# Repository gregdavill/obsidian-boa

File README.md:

# Obsidian Boa #

     ~ Current Status: Prototype boards ordered from OSHPark ~
     
     Note: This design was performed in KiCad nightly , you will need a Nightly build to open and edit these source files.

## Bare PCBs:
Order some PCBs
     [OSHPark](https://oshpark.com/shared_projects/r7u7eQDq)

## What is it?
A simple compact ESP32-S2 development board

Form-factor based off [bitsy-v1.0a](https://github.com/icebreaker-fpga/icebreaker/tree/master/hardware/bitsy-v1.0a)

## What is it?
ESP32-S2 + PSRAM + FLASH

## Licence
 * Hardware in this repository is licenced under Creative Commons BY-SA

 ## OSHW Certification
 TBD (Will apply when prototypes tested)

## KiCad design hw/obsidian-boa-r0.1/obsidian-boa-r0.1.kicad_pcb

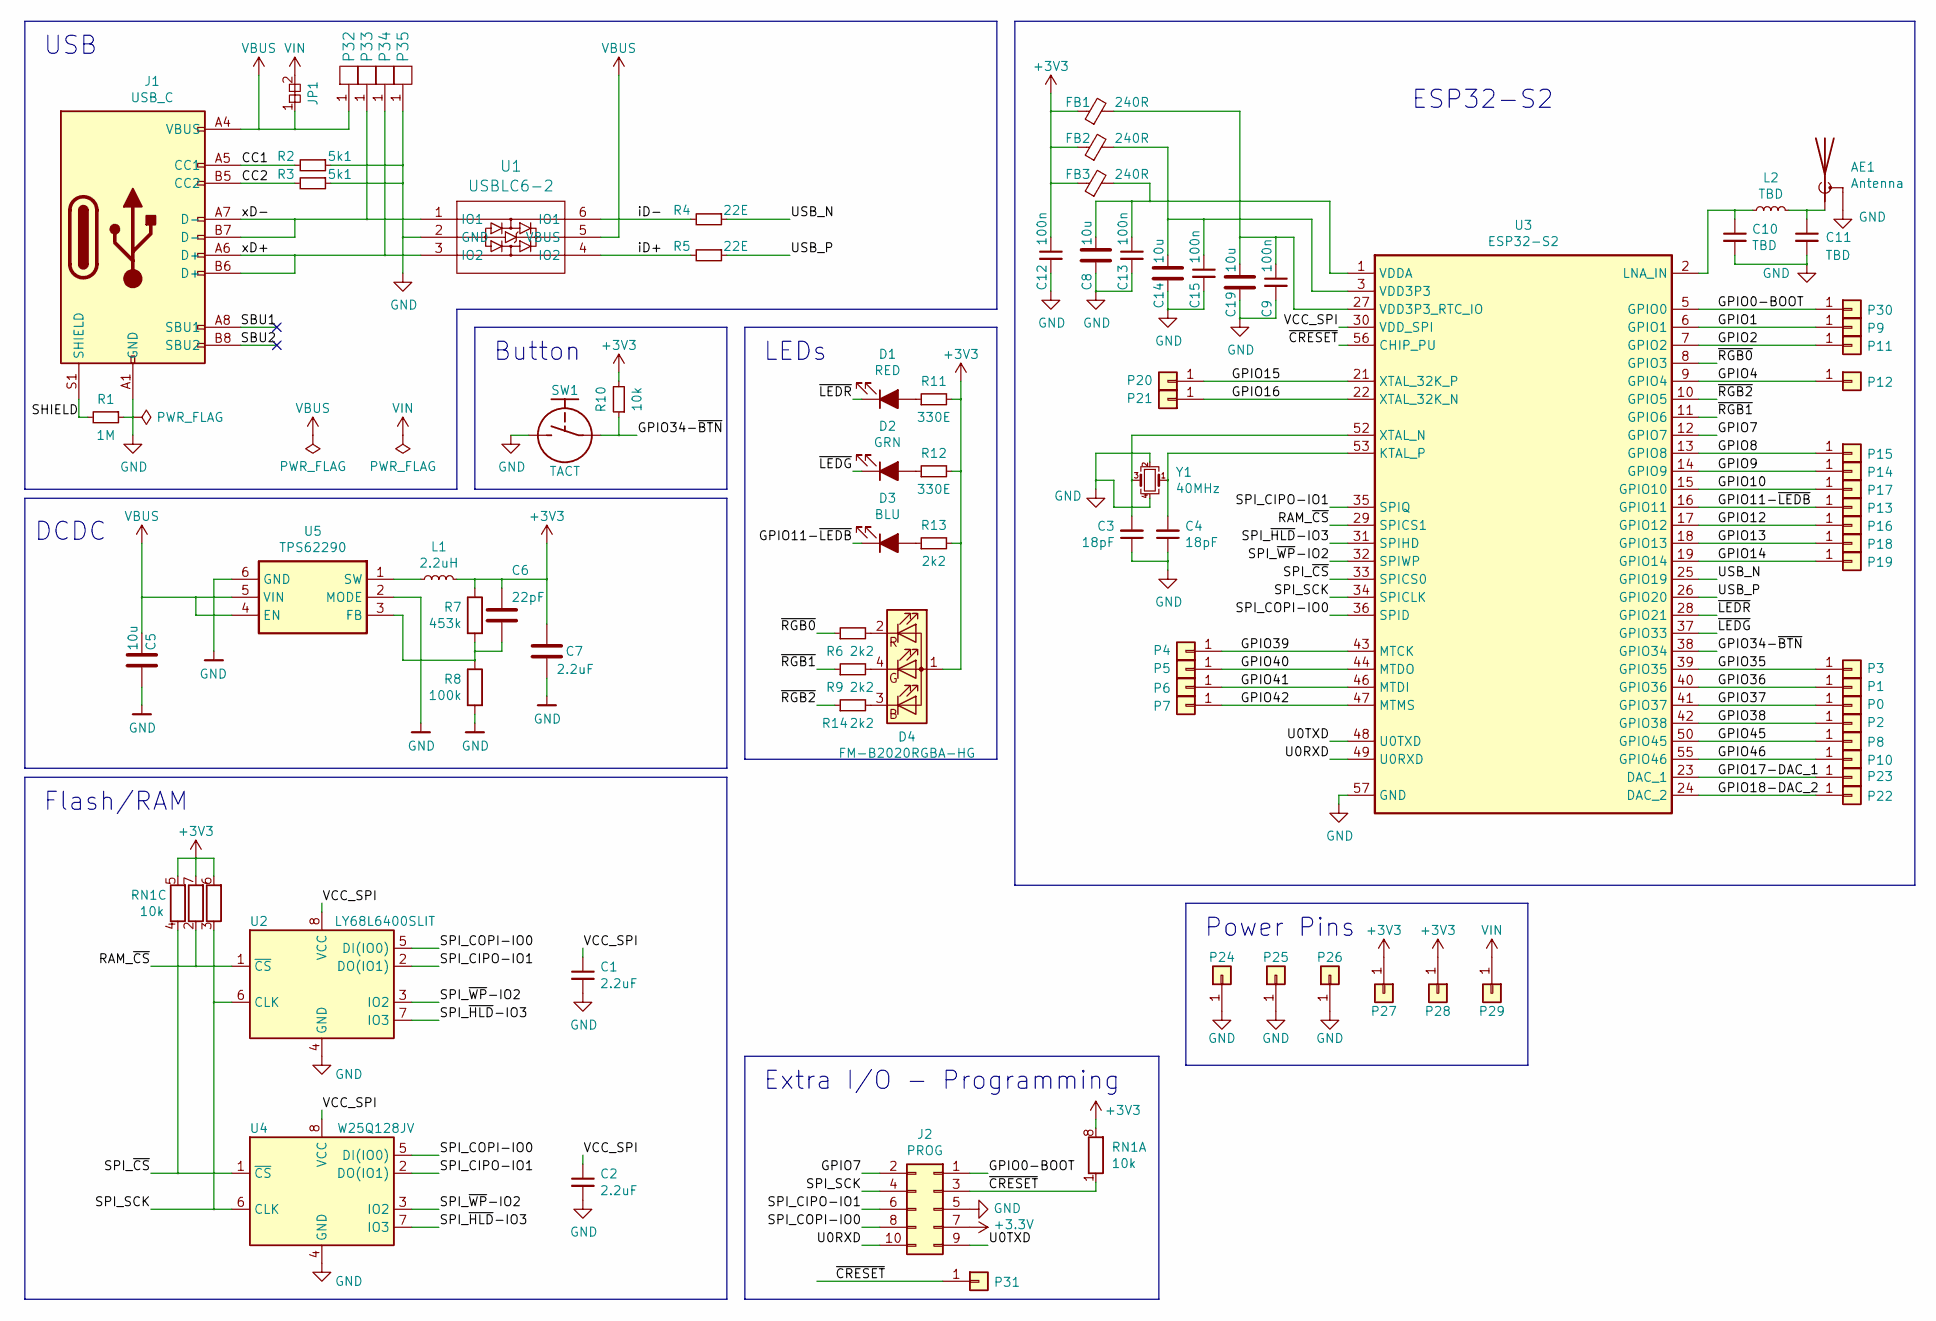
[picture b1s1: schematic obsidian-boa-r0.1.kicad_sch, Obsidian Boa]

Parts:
AE1: Antenna; 0479480001
C1, C2, C7: 2.2uF; C_0402_1005Metric
C3, C4: 18pF; C_0402_1005Metric
C5, C8, C14, C19: 10u; C_0603_1608Metric
C6: 22pF; C_0402_1005Metric
C9, C12, C13, C15: 100n; C_0402_1005Metric
C10, C11: TBD; C_0402_1005Metric
D1: RED; LED_0603_1608Metric_Compact
D2: GRN; LED_0603_1608Metric_Compact
D3: BLU; LED_0603_1608Metric_Compact
D4: FM-B2020RGBA-HG; LED_Lumex_SML-LX0303SIUPGUSB
FB1, FB2, FB3: 240R; L_0402_1005Metric
J1: USB_C; USB_C_Receptacle_HRO_TYPE-C-31-M-12
J2: PROG; PinHeader_2x05_P2.54mm_Vertical_SMD
JP1: Jumper; SolderJumper-2_P1.3mm_Bridged2Bar_RoundedPad1.0x1.5mm
L1: 2.2uH; L_0805_2012Metric
L2: TBD; L_0402_1005Metric
P0: 0; Pin_Header_Straight_Round_1x01_Castellated
P1: 1; Pin_Header_Straight_Round_1x01_Castellated
P2: 2; Pin_Header_Straight_Round_1x01_Castellated
P3: 3; Pin_Header_Straight_Round_1x01_Castellated
P4: 4; Pin_Header_Straight_Round_1x01_Castellated
P5: 5; Pin_Header_Straight_Round_1x01_Castellated
P6: 6; Pin_Header_Straight_Round_1x01_Castellated
P7: 7; Pin_Header_Straight_Round_1x01_Castellated
P8: 8; Pin_Header_Straight_Round_1x01_Castellated
P9: 9; Pin_Header_Straight_Round_1x01_Castellated
P10: 10; Pin_Header_Straight_Round_1x01_Castellated
P11: 11; Pin_Header_Straight_Round_1x01_Castellated
P12: 12; Pin_Header_Straight_Round_1x01_Castellated
P13: 13; Pin_Header_Straight_Round_1x01_Castellated
P14: 14; Pin_Header_Straight_Round_1x01_Castellated
P15: 15; Pin_Header_Straight_Round_1x01_Castellated
P16: 16; Pin_Header_Straight_Round_1x01_Castellated
P17: 17; Pin_Header_Straight_Round_1x01_Castellated
P18: 18; Pin_Header_Straight_Round_1x01_Castellated
P19: 19; Pin_Header_Straight_Round_1x01_Castellated
P20: 20; Pin_Header_Straight_Round_1x01_Castellated
P21: 21; Pin_Header_Straight_Round_1x01_Castellated
P22: 22; Pin_Header_Straight_Round_1x01_Castellated
P23: 23; Pin_Header_Straight_Round_1x01_Castellated
P24, P25, P26: GND; Pin_Header_Straight_Round_1x01_Castellated
P27, P28: 3V3; Pin_Header_Straight_Round_1x01_Castellated
P29: VIN; Pin_Header_Straight_Round_1x01_Castellated
P30: CDONE; Pin_Header_Straight_Round_1x01_Castellated
P31: CRESET; Pin_Header_Straight_Round_1x01_Castellated
P32, P33, P34, P35: UP; PAD_SMD_1x2.65_ROUNDED
R1: 1M; R_0402_1005Metric
R2, R3: 5k1; R_0402_1005Metric
R4, R5: 22E; R_0402_1005Metric
R6, R9, R13, R14: 2k2; R_0402_1005Metric
R7: 453k; R_0402_1005Metric
R8: 100k; R_0402_1005Metric
R10: 10k; R_0402_1005Metric
R11, R12: 330E; R_0402_1005Metric
RN1: 10k; R_Array_Convex_4x0402
SW1: TACT; SW_SPST_3x4x2.5
U1: USBLC6-2; SOT-666
U2: LY68L6400SLIT; SOIC-8_3.9x4.9mm_P1.27mm
U3: ESP32-S2; QFN-56-1EP_7x7mm_P0.4mm_EP5.6x5.6mm
U4: W25Q128JV; SOIC-8_5.23x5.23mm_P1.27mm
U5: TPS62290; WSON-6-1EP_2x2mm_P0.65mm_EP1x1.6mm_ThermalVias
Y1: 40MHz; Crystal_SMD_Abracon_ABM10-4Pin_2.5x2.0mm

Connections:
/CC1: J1.A5 (CC1), R2.2
/CC2: J1.B5 (CC2), R3.2
/GPIO0-BOOT: J2.1, P30.1, U3.5 (GPIO0)
/GPIO1: P9.1, U3.6 (GPIO1)
/GPIO2: P11.1, U3.7 (GPIO2)
/GPIO4: P12.1, U3.9 (GPIO4)
/GPIO7: J2.2, U3.12 (GPIO7)
/GPIO8: P15.1, U3.13 (GPIO8)
/GPIO9: P14.1, U3.14 (GPIO9)
/GPIO10: P17.1, U3.15 (GPIO10)
/GPIO11-~LEDB: D3.1 (K), P13.1, U3.16 (GPIO11)
/GPIO12: P16.1, U3.17 (GPIO12)
/GPIO13: P18.1, U3.18 (GPIO13)
/GPIO14: P19.1, U3.19 (GPIO14)
/GPIO15: P20.1, U3.21 (XTAL_32K_P)
/GPIO16: P21.1, U3.22 (XTAL_32K_N)
/GPIO17-DAC_1: P23.1, U3.23 (DAC_1)
/GPIO18-DAC_2: P22.1, U3.24 (DAC_2)
/GPIO34-~BTN: R10.1, SW1.1, U3.38 (GPIO34)
/GPIO35: P3.1, U3.39 (GPIO35)
/GPIO36: P1.1, U3.40 (GPIO36)
/GPIO37: P0.1, U3.41 (GPIO37)
/GPIO38: P2.1, U3.42 (GPIO38)
/GPIO39: P4.1, U3.43 (MTCK)
/GPIO40: P5.1, U3.44 (MTDO)
/GPIO41: P6.1, U3.46 (MTDI)
/GPIO42: P7.1, U3.47 (MTMS)
/GPIO45: P8.1, U3.50 (GPIO45)
/GPIO46: P10.1, U3.55 (GPIO46)
/RAM_~CS: RN1.2 (R2.1), U2.1 (~CS), U3.29 (SPICS1)
/SHIELD: J1.S1 (SHIELD), R1.2
/SPI_CIPO-IO1: J2.6, U2.2 (DO(IO1)), U3.35 (SPIQ), U4.2 (DO(IO1))
/SPI_COPI-IO0: J2.8, U2.5 (DI(IO0)), U3.36 (SPID), U4.5 (DI(IO0))
/SPI_SCK: J2.4, RN1.3 (R3.1), U2.6 (CLK), U3.34 (SPICLK), U4.6 (CLK)
/SPI_~CS: RN1.4 (R4.1), U3.33 (SPICS0), U4.1 (~CS)
/SPI_~HLD~-IO3: U2.7 (IO3), U3.31 (SPIHD), U4.7 (IO3)
/SPI_~WP~-IO2: U2.3 (IO2), U3.32 (SPIWP), U4.3 (IO2)
/U0RXD: J2.10, U3.49 (U0RXD)
/U0TXD: J2.9, U3.48 (U0TXD)
/USB_N: R4.1, U3.25 (GPIO19)
/USB_P: R5.1, U3.26 (GPIO20)
/VCC_SPI: C1.1, C2.1, U2.8 (VCC), U3.30 (VDD_SPI), U4.8 (VCC)
/iD+: R5.2, U1.4 (IO2)
/iD-: R4.2, U1.6 (IO1)
/xD+: J1.A6 (D+), J1.B6 (D+), P34.1 (PAD), U1.3 (IO2)
/xD-: J1.A7 (D-), J1.B7 (D-), P33.1 (PAD), U1.1 (IO1)
/~CRESET: J2.3, P31.1, RN1.1 (R1.1), U3.56 (CHIP_PU)
/~LEDG: D2.1 (K), U3.37 (GPIO33)
/~LEDR: D1.1 (K), U3.28 (GPIO21)
/~RGB0: R6.1, U3.8 (GPIO3)
/~RGB1: R9.1, U3.11 (GPIO6)
/~RGB2: R14.1, U3.10 (GPIO5)
GND: AE1.2 (Shield), C1.2, C2.2, C3.1, C4.1, C5.2, C7.2, C8.2, C9.2, C10.2, C11.2, C12.2, C13.2, C14.2, C15.2, C19.2, J1.A1 (GND), J1.A12 (GND), J1.B1 (GND), J1.B12 (GND), J2.5, P24.1, P25.1, P26.1, P35.1 (PAD), R1.1, R2.1, R3.1, R8.2, SW1.2, U1.2 (GND), U2.4 (GND), U3.57 (GND), U4.4 (GND), U5.2 (MODE), U5.6 (GND), U5.7 (GND), Y1.2, Y1.4
unnamed: AE1.1 (A), C11.1, L2.2
unnamed: C3.2, U3.52 (XTAL_N), Y1.3
unnamed: C4.2, U3.53 (KTAL_P), Y1.1
unnamed: C6.2, R7.2, R8.1, U5.3 (FB)
unnamed: C10.1, L2.1, U3.2 (LNA_IN)
unnamed: C8.1, C13.1, FB3.2, U3.1 (VDDA), U3.51 (VDDA), U3.54 (VDDA)
unnamed: C14.1, C15.1, FB2.2, U3.3 (VDD3P3), U3.4 (VDD3P3)
unnamed: C9.1, C19.1, FB1.2, U3.20 (VDD3P3_RTC), U3.27 (VDD3P3_RTC_IO), U3.45 (VDD3P3_CPU)
unnamed: D1.2 (A), R11.1
unnamed: D2.2 (A), R12.1
unnamed: D3.2 (A), R13.1
unnamed: D4.2 (RK), R6.2
unnamed: D4.3 (BK), R14.2
unnamed: D4.4 (GK), R9.2
unnamed: L1.1, U5.1 (SW)
VBUS: C5.1, J1.A4 (VBUS), J1.A9 (VBUS), J1.B4 (VBUS), J1.B9 (VBUS), JP1.1, P32.1 (PAD), U1.5 (VBUS), U5.4 (EN), U5.5 (VIN)
VIN: JP1.2, P29.1

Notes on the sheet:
DCDC
USB
Flash/RAM
Button
LEDs
Extra I/O - Programming
Power Pins
ESP32-S2

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
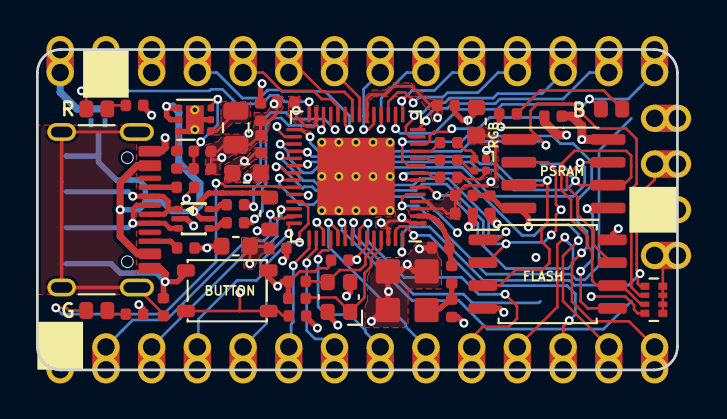
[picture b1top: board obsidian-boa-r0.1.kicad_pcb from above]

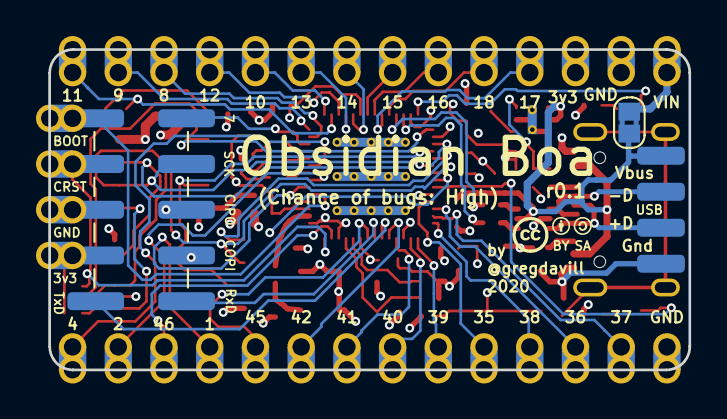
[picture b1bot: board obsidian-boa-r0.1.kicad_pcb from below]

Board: 4 copper layers, 35.6 x 17.8 mm, 87 parts (6 on the bottom side), 71 nets.

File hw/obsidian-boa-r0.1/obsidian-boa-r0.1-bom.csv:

Reference, Quantity, Value, Footprint, Datasheet, Mfg, PN, Source
AE1 ,1,"Antenna","obsidian-boa:0479480001","~","Molex","0479480001",""
C1 C2 C7 ,3,"2.2uF","Capacitor_SMD:C_0402_1005Metric","","Yageo","CC0402MRX5R5BB225",""
C10 C11 ,2,"TBD","Capacitor_SMD:C_0402_1005Metric","","","","ANY"
C3 C4 ,2,"18pF","Capacitor_SMD:C_0402_1005Metric","","Yageo","CC0402GRNPO9BN180",""
C5 C8 C14 C19 ,4,"10u","Capacitor_SMD:C_0603_1608Metric","~","Yageo","CC0603KRX5R5BB106",""
C6 ,1,"22pF","Capacitor_SMD:C_0402_1005Metric","~","Yageo","CC0402KRNPO9BN220",""
C9 C12 C13 C15 ,4,"100n","Capacitor_SMD:C_0402_1005Metric","","Yageo","CC0402ZRY5V7BB104",""
D1 ,1,"RED","obsidian-boa:LED_0603_1608Metric_Compact","","Lite-On Inc.","LTST-C191KRKT",""
D2 ,1,"GRN","obsidian-boa:LED_0603_1608Metric_Compact","","Lite-On Inc.","LTST-C191KGKT",""
D3 ,1,"BLU","obsidian-boa:LED_0603_1608Metric_Compact","","Lite-On Inc.","LTST-C191TBKT",""
D4 ,1,"FM-B2020RGBA-HG","LED_SMD:LED_Lumex_SML-LX0303SIUPGUSB","~"
FB1 FB2 FB3 ,3,"240R","Inductor_SMD:L_0402_1005Metric","~","Murata Electronics","BLM15BC241SN1D",""
J1 ,1,"USB_C","pkl_connectors:USB_C_Receptacle_HRO_TYPE-C-31-M-12","https://www.usb.org/sites/default/files/documents/usb_type-c.zip","GCT","USB4105-GF-A",""
J2 ,1,"PROG","pkl_pin_headers:PinHeader_2x05_P2.54mm_Vertical_SMD","~"
JP1 ,1,"Jumper","Jumper:SolderJumper-2_P1.3mm_Bridged2Bar_RoundedPad1.0x1.5mm","","","","ANY"
L1 ,1,"2.2uH","Inductor_SMD:L_0805_2012Metric","~"
L2 ,1,"TBD","Inductor_SMD:L_0402_1005Metric","~"
P0 ,1,"0","pkl_pin_headers:Pin_Header_Straight_Round_1x01_Castellated","~","","","ANY"
P1 ,1,"1","pkl_pin_headers:Pin_Header_Straight_Round_1x01_Castellated","~","","","ANY"
P10 ,1,"10","pkl_pin_headers:Pin_Header_Straight_Round_1x01_Castellated","~","","","ANY"
P11 ,1,"11","pkl_pin_headers:Pin_Header_Straight_Round_1x01_Castellated","~","","","ANY"
P12 ,1,"12","pkl_pin_headers:Pin_Header_Straight_Round_1x01_Castellated","~","","","ANY"
P13 ,1,"13","pkl_pin_headers:Pin_Header_Straight_Round_1x01_Castellated","~","","","ANY"
P14 ,1,"14","pkl_pin_headers:Pin_Header_Straight_Round_1x01_Castellated","~","","","ANY"
P15 ,1,"15","pkl_pin_headers:Pin_Header_Straight_Round_1x01_Castellated","~","","","ANY"
P16 ,1,"16","pkl_pin_headers:Pin_Header_Straight_Round_1x01_Castellated","~","","","ANY"
P17 ,1,"17","pkl_pin_headers:Pin_Header_Straight_Round_1x01_Castellated","~","","","ANY"
P18 ,1,"18","pkl_pin_headers:Pin_Header_Straight_Round_1x01_Castellated","~","","","ANY"
P19 ,1,"19","pkl_pin_headers:Pin_Header_Straight_Round_1x01_Castellated","~","","","ANY"
P2 ,1,"2","pkl_pin_headers:Pin_Header_Straight_Round_1x01_Castellated","~","","","ANY"
P20 ,1,"20","pkl_pin_headers:Pin_Header_Straight_Round_1x01_Castellated","~","","","ANY"
P21 ,1,"21","pkl_pin_headers:Pin_Header_Straight_Round_1x01_Castellated","~","","","ANY"
P22 ,1,"22","pkl_pin_headers:Pin_Header_Straight_Round_1x01_Castellated","~","","","ANY"
P23 ,1,"23","pkl_pin_headers:Pin_Header_Straight_Round_1x01_Castellated","~","","","ANY"
P24 P25 P26 ,3,"GND","pkl_pin_headers:Pin_Header_Straight_Round_1x01_Castellated","~","","","ANY"
P27 P28 ,2,"3V3","pkl_pin_headers:Pin_Header_Straight_Round_1x01_Castellated","~","","","ANY"
P29 ,1,"VIN","pkl_pin_headers:Pin_Header_Straight_Round_1x01_Castellated","~","","","ANY"
P3 ,1,"3","pkl_pin_headers:Pin_Header_Straight_Round_1x01_Castellated","~","","","ANY"
P30 ,1,"CDONE","pkl_pin_headers:Pin_Header_Straight_Round_1x01_Castellated","~","","","ANY"
P31 ,1,"CRESET","pkl_pin_headers:Pin_Header_Straight_Round_1x01_Castellated","~","","","ANY"
P32 P33 P34 P35 ,4,"UP","pkl_pads:PAD_SMD_1x2.65_ROUNDED","","","","ANY"
P4 ,1,"4","pkl_pin_headers:Pin_Header_Straight_Round_1x01_Castellated","~","","","ANY"
P5 ,1,"5","pkl_pin_headers:Pin_Header_Straight_Round_1x01_Castellated","~","","","ANY"
P6 ,1,"6","pkl_pin_headers:Pin_Header_Straight_Round_1x01_Castellated","~","","","ANY"
P7 ,1,"7","pkl_pin_headers:Pin_Header_Straight_Round_1x01_Castellated","~","","","ANY"
P8 ,1,"8","pkl_pin_headers:Pin_Header_Straight_Round_1x01_Castellated","~","","","ANY"
P9 ,1,"9","pkl_pin_headers:Pin_Header_Straight_Round_1x01_Castellated","~","","","ANY"
R1 ,1,"1M","Resistor_SMD:R_0402_1005Metric","","Yageo","RC0402FR-071ML",""
R10 ,1,"10k","Resistor_SMD:R_0402_1005Metric","","Yageo","RC0402FR-0710KL",""
R11 R12 ,2,"330E","Resistor_SMD:R_0402_1005Metric","","Yageo","RC0402FR-07330RL",""
R2 R3 ,2,"5k1","Resistor_SMD:R_0402_1005Metric","","Yageo","RC0402FR-075K1L",""
R4 R5 ,2,"22E","Resistor_SMD:R_0402_1005Metric","","Yageo","RC0402FR-0722RL",""
R6 R9 R13 R14 ,4,"2k2","Resistor_SMD:R_0402_1005Metric","","Yageo","RC0402FR-072K2L",""
R7 ,1,"453k","Resistor_SMD:R_0402_1005Metric","~","Yageo","RC0402FR-07453KL",""
R8 ,1,"100k","Resistor_SMD:R_0402_1005Metric","~","Yageo","RC0402FR-07100KL",""
RN1 ,1,"10k","Resistor_SMD:R_Array_Convex_4x0402","~"
SW1 ,1,"TACT","pkl_buttons_switches:SW_SPST_3x4x2.5",""
U1 ,1,"USBLC6-2","pkl_housings_sot:SOT-666","","STMicroelectronics","USBLC6-2P6",""
U2 ,1,"W25Q32JVSS","Package_SO:SOIC-8_3.9x4.9mm_P1.27mm","http://www.winbond.com/resource-files/w25q32jv%20revg%200327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"
U3 ,1,"ESP32-S2","Package_DFN_QFN:QFN-56-1EP_7x7mm_P0.4mm_EP5.6x5.6mm","","Espressif Systems","ESP32-S2",""
U4 ,1,"W25Q32JVSS","Package_SO:SOIC-8_5.23x5.23mm_P1.27mm","http://www.winbond.com/resource-files/w25q32jv%20revg%200327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","Winbond Electronics","W25Q128JVSIQ TR",""
U5 ,1,"TPS62290","Package_SON:WSON-6-1EP_2x2mm_P0.65mm_EP1x1.6mm_ThermalVias","","Texas Instruments","TPS62290DRVR",""
Y1 ,1,"40MHz","Crystal:Crystal_SMD_Abracon_ABM10-4Pin_2.5x2.0mm","~","ECS Inc.","ECS-400-10-36B-CKY-TR",""

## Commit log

2020-07-06 Added readme
2020-07-06 hw.r0d1: initial commit of KiCad project
2020-07-07 hw.r0d1: Tidy up schematic, plan out layout on PCB
2020-07-07 doc: Update Licence to CC-BY-SA
2020-07-07 hw.r0d1: Update routing and layout
2020-07-07 hw.r0d1: Complete first pass of layout and routing
2020-07-07 hw.r0d1: Update 3d models, included 3d render
2020-07-07 hw.r0d1: Cleanup repo
2020-07-07 hw.r0d1: Update 3d files to relative paths
2020-07-08 hw.r0d1: update to route VDD_SPI seperately.
2020-07-09 docs: Update readme
2020-07-18 hw.r0d1: Update BOM fields
2020-07-18 hw.r0d1: Add Gerbers
2020-08-13 Added a PDF of schematic
2020-08-15 Added JPG with I/O pin names.
2020-08-15 Added label for button to JPG
2020-10-31 hw: Update PSRAM/FLASH part numbers
    - Regenerate schematic
    - Add generated BOM
    #6
2020-11-09 hw: Sync PCB to schematic
    Fixes #7
2021-03-25 hw.r0d1: Create Production outputs

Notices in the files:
hw/obsidian-boa-r0.1/obsidian-boa-r0.1.kicad_pcb:
© 2020 Greg Davill
License: CC BY-SA 4.0
